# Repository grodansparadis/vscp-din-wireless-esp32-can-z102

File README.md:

# vscp-din-wireless-esp32-can-z102

This board has secure wireless wifi gateway functionality for a remote **CAN4VSCP** bus.

Part of the [VSCP Project](https://www.vscp.org).

Copyright 2021-2026 (C) Åke Hedman, [https://www.grodansparadis.com](Grodans Paradis AB)
Licensed under the MIT License. See LICENSE file in the project root for full license information.

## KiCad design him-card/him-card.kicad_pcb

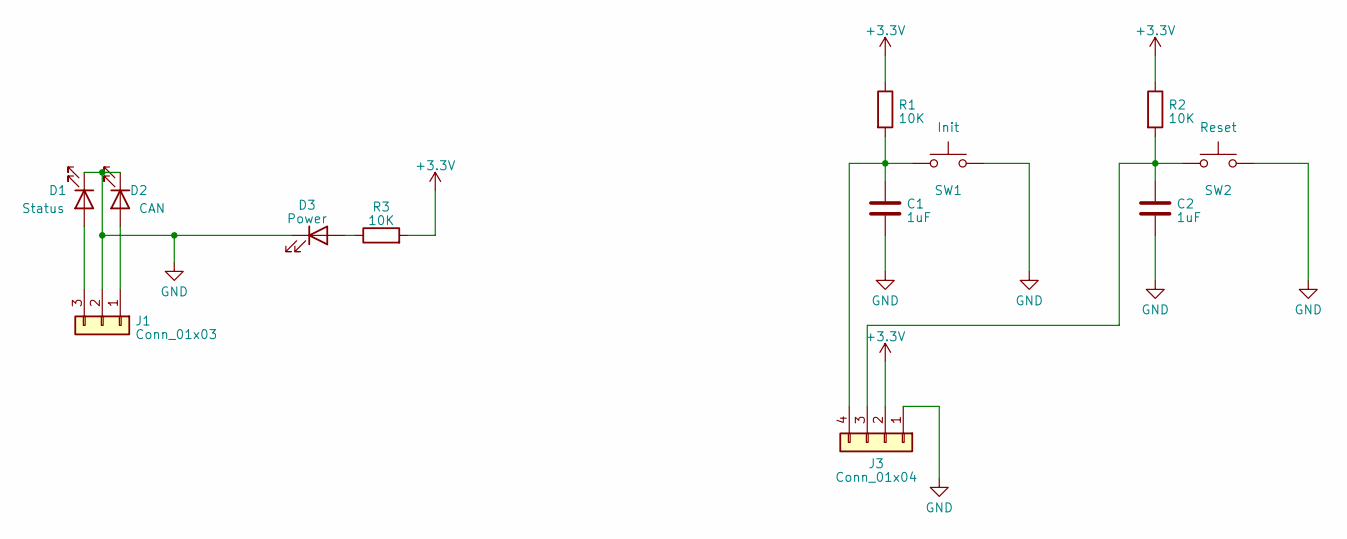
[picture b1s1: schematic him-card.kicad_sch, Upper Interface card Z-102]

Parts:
C1, C2: 1uF; C_0805_2012Metric_Pad1.18x1.45mm_HandSolder
D1: Status; LED_D3.0mm
D2: CAN; LED_D3.0mm
D3: Power; LED_D3.0mm
J1: Conn_01x03; PinHeader_1x03_P2.54mm_Vertical
J3: Conn_01x04; PinHeader_1x04_P2.54mm_Vertical
R1, R2, R3: 10K; R_0805_2012Metric_Pad1.20x1.40mm_HandSolder
SW1: Init; SW_Tactile_Straight_KSL0Axx1LFTR
SW2: Reset; SW_Tactile_Straight_KSL0Axx1LFTR

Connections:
+3.3V: J3.2, R1.1, R2.1, R3.2
GND: C1.2, C2.2, D1.1 (K), D2.1 (K), D3.1 (K), J1.2, J3.1, SW1.2, SW2.2
unnamed: D1.2 (A), J1.3
unnamed: D2.2 (A), J1.1
unnamed: D3.2 (A), R3.1
unnamed: C2.1, J3.3, R2.2, SW2.1
unnamed: C1.1, J3.4, R1.2, SW1.1

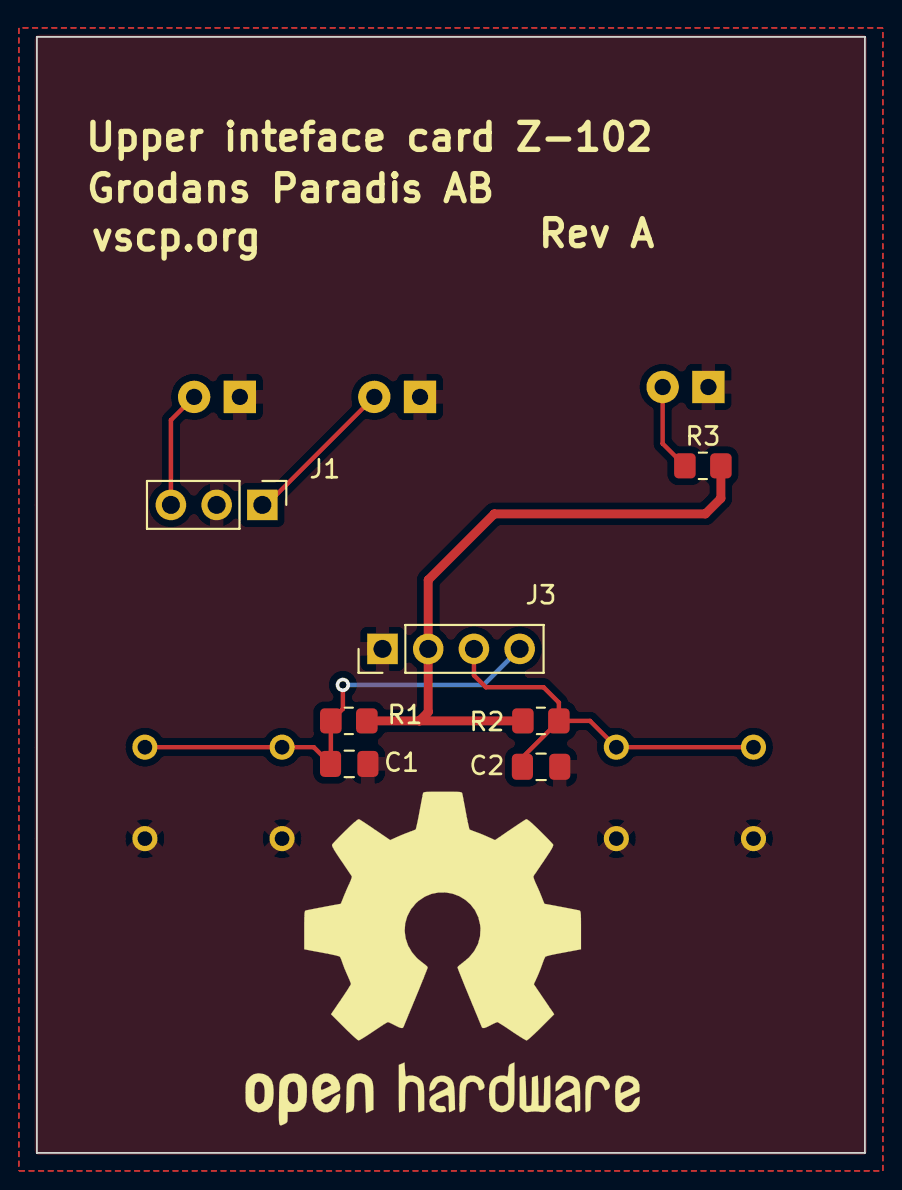
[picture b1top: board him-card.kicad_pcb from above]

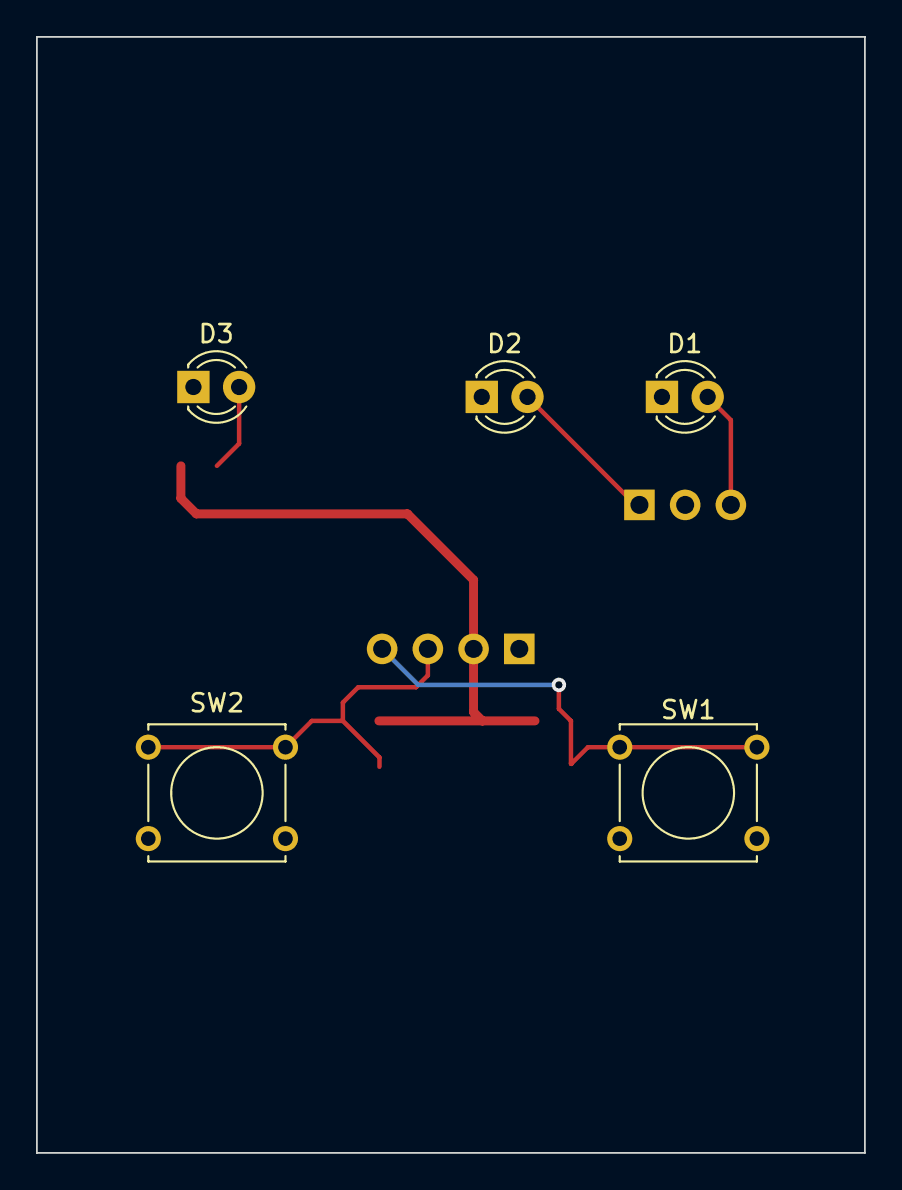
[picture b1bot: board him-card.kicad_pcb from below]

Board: 2 copper layers, 46.0 x 62.0 mm, 12 parts (5 on the bottom side), 7 nets.

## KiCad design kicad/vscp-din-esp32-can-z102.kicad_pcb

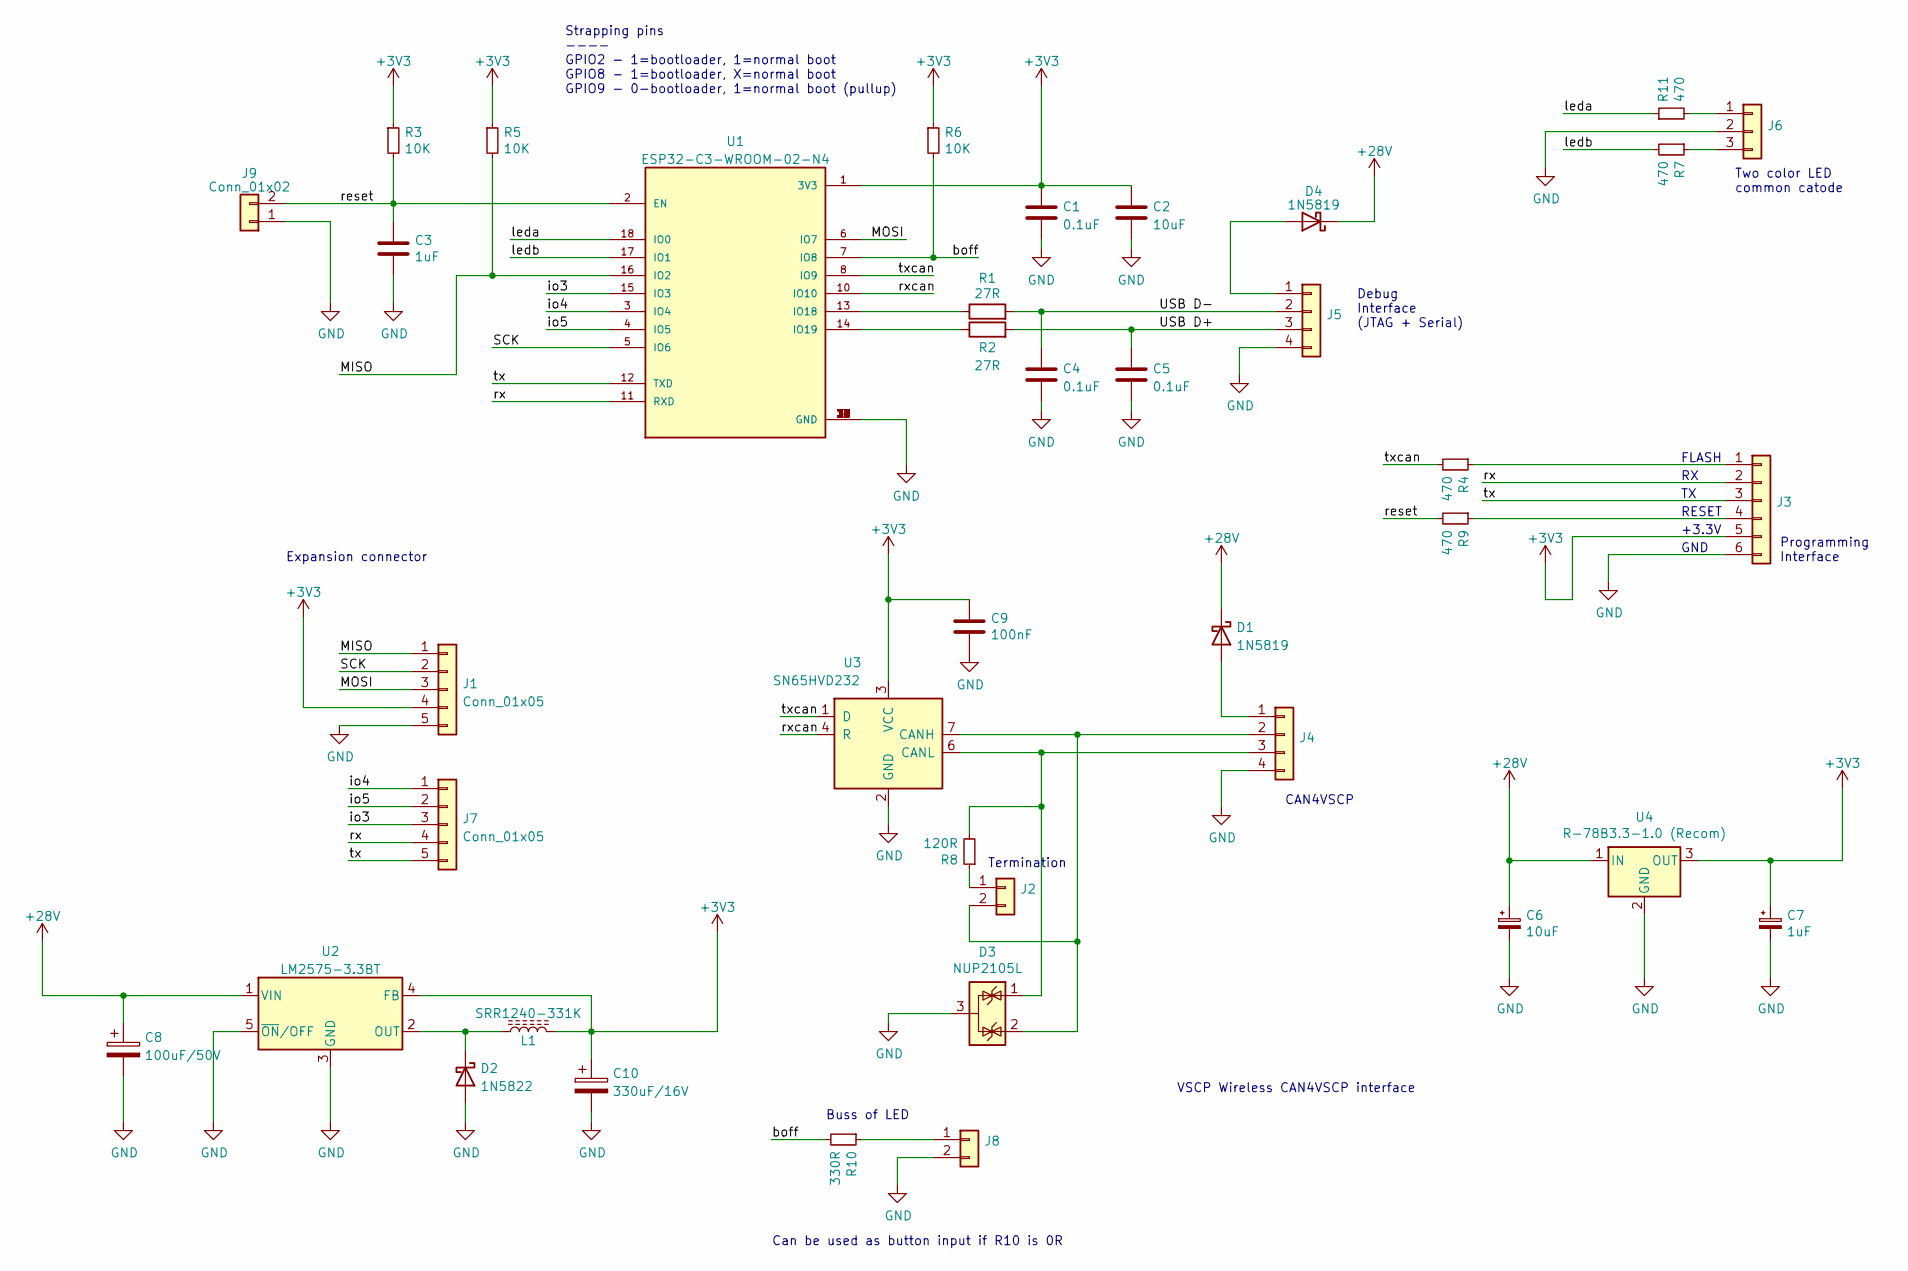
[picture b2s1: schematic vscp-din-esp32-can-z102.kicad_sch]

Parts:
C1, C4, C5: 0.1uF; C_0805_2012Metric_Pad1.18x1.45mm_HandSolder
C2, C6: 10uF; C_0805_2012Metric_Pad1.18x1.45mm_HandSolder
C3, C7: 1uF; C_0805_2012Metric_Pad1.18x1.45mm_HandSolder
C8: 100uF/50V; CP_Elec_6.3x9.9
C9: 100nF; C_0805_2012Metric_Pad1.18x1.45mm_HandSolder
C10: 330uF/16V; CP_Elec_6.3x9.9
D1, D4: 1N5819; D_SOD-123
D2: 1N5822; D_SMA_Handsoldering
D3: NUP2105L; SOT-23_Handsoldering
J1, J7: Conn_01x05; PinHeader_1x05_P2.54mm_Vertical
J2, J8, J9: Conn_01x02; PinHeader_1x02_P2.54mm_Vertical
J3: Conn_01x06; PinHeader_1x06_P2.54mm_Vertical
J4: Conn_01x04; PhoenixContact_MC_1,5_4-G-3.81_1x04_P3.81mm_Horizontal
J5: Conn_01x04; PinHeader_1x04_P2.54mm_Vertical
J6: Conn_01x03; PinHeader_1x03_P2.54mm_Vertical
L1: SRR1240-331K; L_Bourns_SRR1260
R1, R2: 27R; R_0805_2012Metric_Pad1.20x1.40mm_HandSolder
R3, R5, R6: 10K; R_0805_2012Metric_Pad1.20x1.40mm_HandSolder
R4, R9: 470; R_0805_2012Metric_Pad1.20x1.40mm_HandSolder
R7, R11: 470; R_0805_2012Metric
R8: 120R; R_0805_2012Metric_Pad1.20x1.40mm_HandSolder
R10: 330R; R_0805_2012Metric_Pad1.20x1.40mm_HandSolder
U1: ESP32-C3-WROOM-02-N4; ESP-WROOM-02
U2: LM2575-3.3BT; TO-263-5_TabPin3
U3: SN65HVD232; SOIC-8_3.9x4.9mm_P1.27mm
U4: R-78B3.3-1.0 (Recom); Converter_DCDC_RECOM_R-78B-2.0_THT

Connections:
+3V3: C1.1, C2.1, C7.1, C9.1, C10.1, J1.4, J3.5, L1.2, R3.1, R5.1, R6.1, U1.1 (3V3), U2.4 (FB), U3.3 (VCC), U4.3 (OUT)
+28V: C6.1, C8.1, D1.1 (K), D4.1 (K), U2.1 (VIN), U4.1 (IN)
/MISO: J1.1, R5.2, U1.16 (IO2)
/MOSI: J1.3, U1.6 (IO7)
/SCK: J1.2, U1.5 (IO6)
/USB D+: C5.1, J5.3, R2.2
/USB D-: C4.1, J5.2, R1.2
/boff: R6.2, R10.2, U1.7 (IO8)
/io3: J7.3, U1.15 (IO3)
/io4: J7.1, U1.3 (IO4)
/io5: J7.2, U1.4 (IO5)
/leda: R11.1, U1.18 (IO0)
/ledb: R7.2, U1.17 (IO1)
/reset: C3.1, J9.2, R3.2, R9.2, U1.2 (EN)
/rx: J3.2, J7.4, U1.11 (RXD)
/rxcan: U1.10 (IO10), U3.4 (R)
/tx: J3.3, J7.5, U1.12 (TXD)
/txcan: R4.2, U1.8 (IO9), U3.1 (D)
GND: C1.2, C2.2, C3.2, C4.2, C5.2, C6.2, C7.2, C8.2, C9.2, C10.2, D2.2 (A), D3.3 (A), J1.5, J3.6, J4.4, J5.4, J6.2, J8.2, J9.1, U1.9 (GND), U1.19 (GND), U1.20 (GND), U1.21 (GND), U1.22 (GND), U1.23 (GND), U1.24 (GND), U1.25 (GND), U1.26 (GND), U1.27 (GND), U1.28 (GND), U1.29 (GND), U1.30 (GND), U1.31 (GND), U1.32 (GND), U1.33 (GND), U1.34 (GND), U1.35 (GND), U1.36 (GND), U1.37 (GND), U1.38 (GND), U1.39 (GND), U2.3 (GND), U2.5 (~ON/OFF), U3.2 (GND), U4.2 (GND)
unnamed: D1.2 (A), J4.1
unnamed: D2.1 (K), L1.1, U2.2 (OUT)
unnamed: D4.2 (A), J5.1
unnamed: J2.1, R8.1
unnamed: D3.2 (K), J2.2, J4.2, U3.7 (CANH)
unnamed: J3.1, R4.1
unnamed: J3.4, R9.1
unnamed: D3.1 (K), J4.3, R8.2, U3.6 (CANL)
unnamed: J6.1, R11.2
unnamed: J6.3, R7.1
unnamed: J8.1, R10.1
unnamed: R1.1, U1.13 (IO18)
unnamed: R2.1, U1.14 (IO19)

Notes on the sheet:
VSCP Wireless CAN4VSCP interface
Termination
RESET
CAN4VSCP
Debug Interface (JTAG + Serial)
Buss of LED
Can be used as button input if R10 is 0R
Strapping pins ---- GPIO2 - 1=bootloader, 1=normal boot GPIO8 - 1=bootloader, X=normal boot GPIO9 - 0-bootloader, 1=normal boot (pullup)
+3.3V
Programming Interface
GND
Two color LED common catode
FLASH
Expansion connector

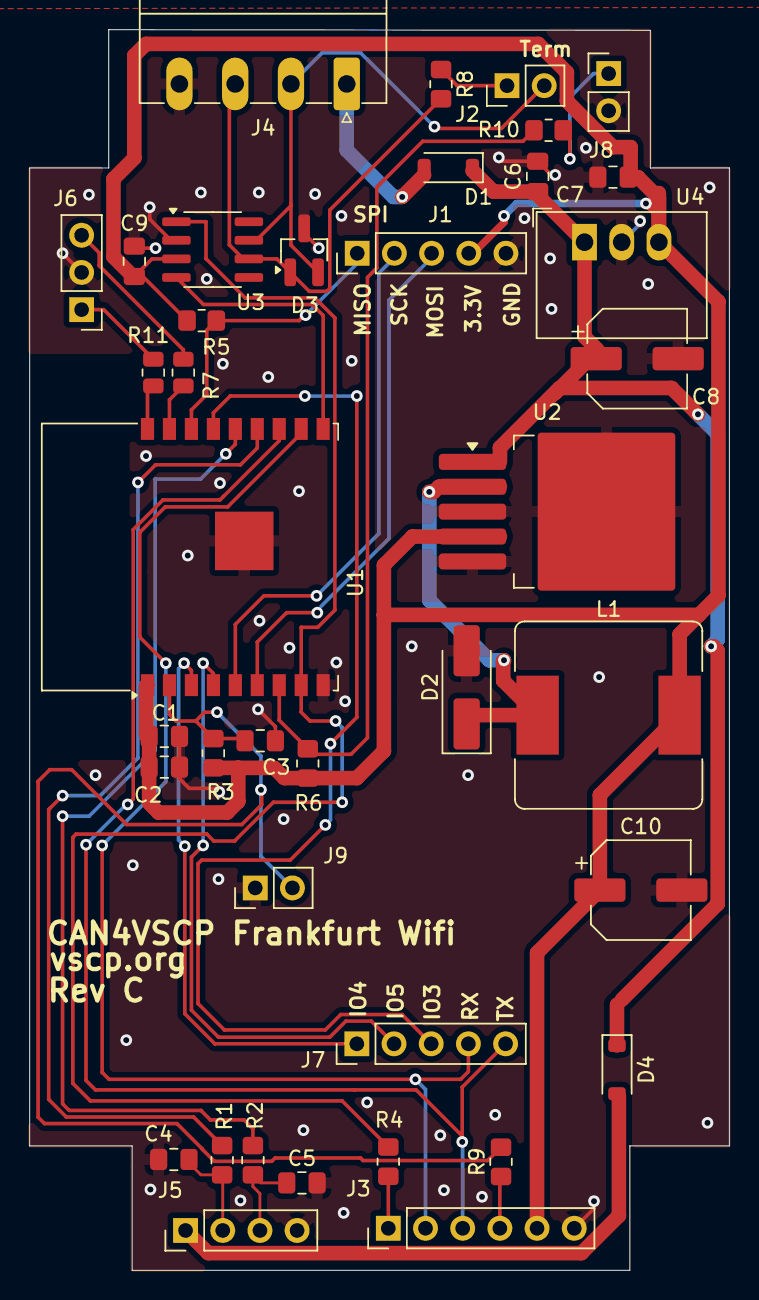
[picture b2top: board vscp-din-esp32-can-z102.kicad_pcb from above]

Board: 2 copper layers, 47.8 x 84.8 mm, 39 parts (0 on the bottom side), 32 nets.

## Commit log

2022-09-02 Initial checkin
2022-09-02 Removed unused images
2022-09-02 Added project description
2022-09-09 Added esp-idf standard can examples as starting points
2022-09-09 Moved schemas to kiad folder
2022-09-10 rev b schame started canrx moved from gpio10 to gpio3
2022-09-10 Added images for rev B
2022-09-11 Added provisioning code
2022-09-14 First part of tcpipsrv
2022-09-16 txcan routed to Flash pin instead of io8
2022-09-16 Updated schema picture
2022-09-20 J4 moved closer to edge.
2022-09-25 Added connector and resistor for BUS_OFF LED connector.
2022-09-25 Fixed spelling
2022-09-28 Changed structure for VCSP Link Protocol Task
2022-09-29 Send/receive events implemented
2023-03-06 Updated copyright year
2023-04-25 Rev B away for production
2025-02-18 Updated copyright for some old stuff
2025-02-18 Updated schema to latest KiCAD
2025-02-19 Added buildfiles
2025-02-19 vscp firmware is now submodule
2025-02-19 Removing UDP, WS and BT
2025-02-20 Updated VSCP link callbacks to work in rcvloop mode
2025-02-21 VSCP tcp/ip link protocol working
2025-02-21 Change places for interfaces 0000 is unit, 0001 is CAN4VSCP
2025-09-17 Added missing firmware files
2025-09-23 Added folder for design documents
2026-01-29 CAN <-> vscp-link working
2026-02-03 Added multicast skeletons
2026-02-04 Configuration in place
2026-02-06 Configuration interface fixed
2026-02-10 CVhanged lowest Ubuntu workspace build
2026-02-10 Added CAN setup section. Added accesspoint parameter settings
2026-02-10 config options for MQTT QoS and retain
2026-02-11 Added MQTT receive with topic substitution
2026-02-12 Updated twai to the new api
2026-02-12 Added build workflow
2026-02-12 Testing workflow
2026-02-12 CI: set ESP32-C3 flash size to 4MB in [sdkconfig.defaults](http://_vscodecontentref_/0)
2026-02-13 submodule vscp-firmware updated to latest
2026-02-13 XML format now supports JSON & STRING
2026-02-13 Binary MQTT send added
2026-02-17 Updated submodule
2026-02-19 MQTT send/receive fully in place
2026-02-20 Initial udp functionality in place
2026-02-23 Clean and encrypted UDP receive/send in place
2026-02-23 Added combo to select encryption level (one level for all)
2026-02-25 Multicast interface fully in place
2026-03-02 Added initial websockets ws1 functionality
2026-03-02 Added hook for websocket and enabled functionality
2026-03-02 Added missing include file
2026-03-02 Actually using sdkconfig
2026-03-09 Authentication callback fixed
2026-03-19 Fixed memory leak
2026-03-19 Added CAN console <-> ws1
2026-03-20 Added CAN console with discovery
2026-03-20 Added build versioning
2026-03-20 Added python increment file
2026-03-20 Fixed workflow
2026-03-20 Removed some warnings
2026-03-24 Updated coded for esp-idf v6.0
2026-03-25 All binary function codes handled.
2026-03-27 All binary calls in place
2026-03-27 All callback embryous in place
2026-03-30 Added label for z102
2026-03-30 Removed backup files from git
2026-03-31 Add focused Codacy workflow and remove tracked key
2026-03-31 Document example certificate key convention
2026-03-31 Moved the context pointer to the first argument of functions to be consistent
2026-03-31 Initial code added for binary callbacks
2026-04-07 Added code of conduct
2026-04-09 ws1: fix encrypted binary frame parsing and length recovery
2026-04-09 build: track dependencies lock and untrack managed components
2026-04-09 Added binary tests
2026-04-09 test: add C binary WS1 smoke test (scenarios A/B/C)
2026-04-09 Binary test written in C
2026-04-09 chore: update vscode approved commands
2026-04-09 firmware: migrate CRC refs to vscp-crc names
2026-04-09 firmware: pin vscp-firmware CRC macro fix
2026-04-09 Binary protocol all tests pass
2026-04-09 Log view added to web interface
2026-04-09 Added codacy cli support
2026-04-09 Fixed minor possible problems
2026-04-10 Fixed som info values
2026-04-10 Fixed printf format error
2026-04-13 Option to log to MQTT and UDP
2026-04-13 strengthened the disabled styling
2026-04-13 Backup/restore of persistent data added
2026-04-13 improved wev i/f looks
2026-04-13 Minor layout fix
2026-04-14 removed main menu button from start page
2026-04-24 Fixed statistics for CAN
2026-04-27 Defined status LED colors
2026-04-29 Updated schema
2026-05-29 Bump ws from 8.19.0 to 8.20.1 in /firmware/test/ws
    Bumps [ws](https://github.com/websockets/ws) from 8.19.0 to 8.20.1.
    - [Release notes](https://github.com/websockets/ws/releases)
    - [Commits](https://github.com/websockets/ws/compare/8.19.0...8.20.1)
    ---
    updated-dependencies:
    - dependency-name: ws
2026-06-09 Added simplified help message
2026-06-23 Bump ws from 8.19.0 to 8.21.0 in /firmware/test/ws
    Bumps [ws](https://github.com/websockets/ws) from 8.19.0 to 8.21.0.
    - [Release notes](https://github.com/websockets/ws/releases)
    - [Commits](https://github.com/websockets/ws/compare/8.19.0...8.21.0)
    ---
    updated-dependencies:
    - dependency-name: ws
